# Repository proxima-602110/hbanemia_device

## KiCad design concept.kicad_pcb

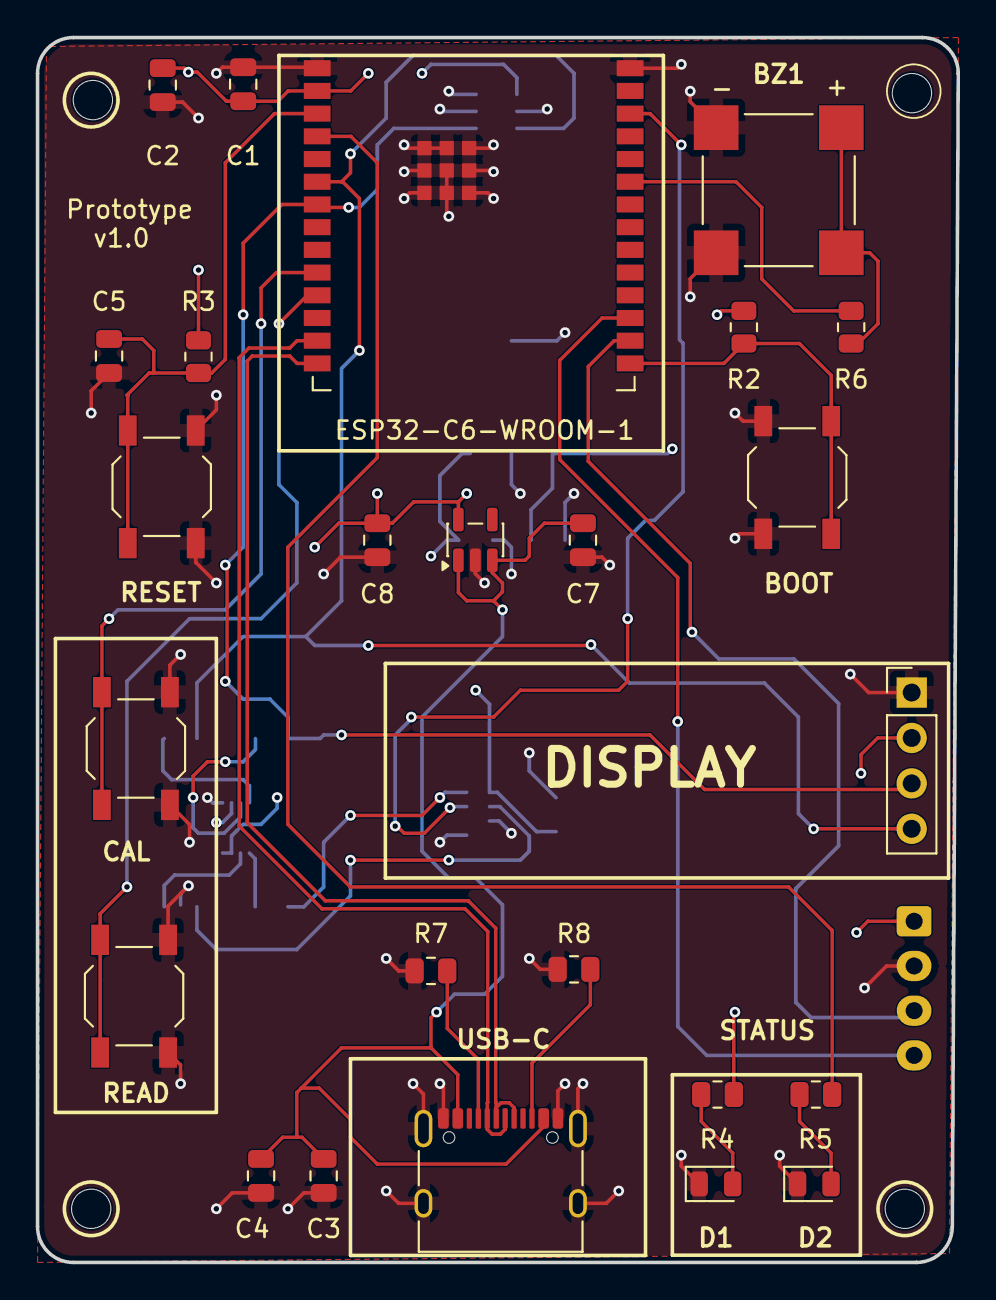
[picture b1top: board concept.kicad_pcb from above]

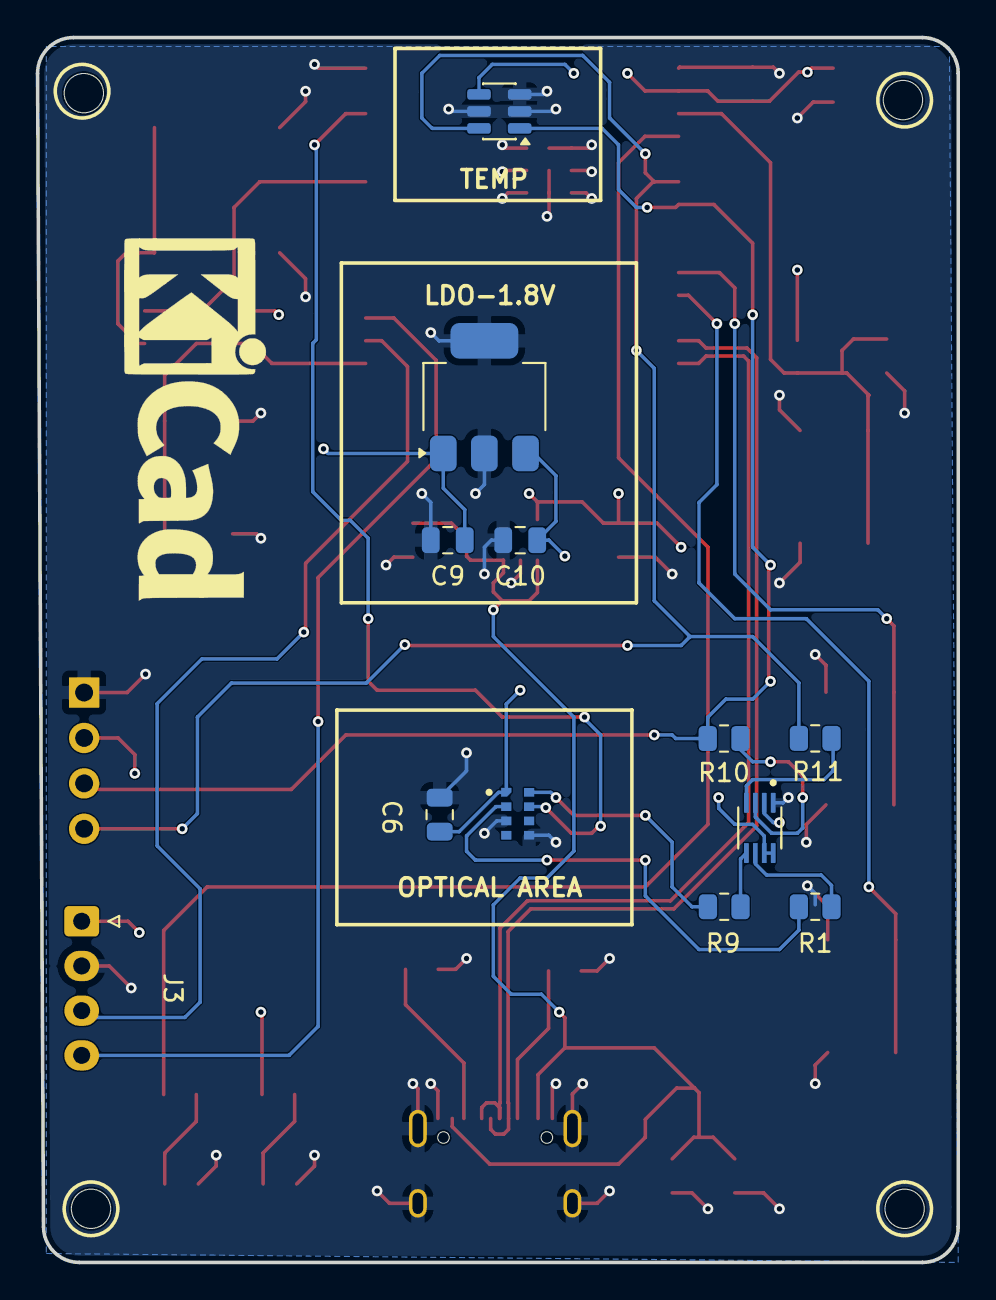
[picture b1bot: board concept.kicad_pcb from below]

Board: 4 copper layers, 51.5 x 68.5 mm, 41 parts (12 on the bottom side), 28 nets.

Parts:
BZ1: Buzzer; XDCR_CMT-8504-100-SMT-TR
C1, C4, C5, C6: 0.1u; C_0805_2012Metric
C2, C3, C9, C10: 10u; C_0805_2012Metric
C7, C8: 1u; C_0805_2012Metric
D1: PWR; LED_0805_2012Metric
D2: Wi-Fi; LED_0805_2012Metric
H1, H2, H3, H4: MountingHole; MountingHole_2.2mm_M2
J1: USB_C_Receptacle_USB2.0_16P; USB_C_Receptacle_XKB_U262-16XN-4BVC11
J2: Conn_01x04; PinHeader_1x04_P2.54mm_Vertical
J3: Conn_01x04; JST_XH_S4B-XH-A-1_1x04_P2.50mm_Horizontal
R1, R9, R10, R11: 4.7k; R_0805_2012Metric
R2, R3: 10k; R_0805_2012Metric
R4, R5, R6: 220; R_0805_2012Metric
R7, R8: 5.1k; R_0805_2012Metric
SW1, SW2, SW3, SW4: SW_Push; SW_SPST_TL3342
U1: AP2112K-3.3; SOT-23-5
U2: AS7341DLG; XDCR_AS7341-DLGM
U3: TMP100; SOT-23-6
U4: LT1963AxST-1.8; SOT-223-3_TabPin2
U5: PCA9306; SOP50P310X90-8N
U6: ESP32-C6-WROOM-1

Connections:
+1.8V: C6.1, C10.1, U2.1 (VDD), U4.3 (OUT), U5.2 (VREF1)
+3.3V: C1.1, C2.1, C8.1, C9.1, J2.2, J3.1, R2.1, R3.1, R4.2, U1.5 (VOUT), U3.4 (V+), U4.1 (IN), U5.7 (VREF2), U5.8 (EN), U6.2 (3V3)
/BOOT: R2.2, SW2.1, U6.15 (GPIO9)
/EN: C5.1, R3.2, SW1.1, U6.3 (EN/CHIP_PU)
/IO3: U2.7 (INT), U6.26 (GPIO3/ADC1_CH3)
/IO4: R5.2, U6.4 (MTMS/GPIO4/ADC1_CH4)
/IO6: J2.4, R11.1, U3.6 (SDA), U6.6 (MTCK/GPIO6/ADC1_CH6)
/IO7: J2.3, R10.1, U3.1 (SCL), U6.7 (MTDO/GPIO7)
/IO10: SW4.1, U6.10 (GPIO8)
/IO11: SW3.1, U6.11 (GPIO10)
/IO15: R6.2, U6.23 (GPIO15)
/LED_560: J3.3, U6.16 (GPIO18)
/LED_850: J3.4, U6.17 (GPIO19)
/USB_D+: J1.A6 (D+), J1.B6 (D+), U6.14 (GPIO13/USB_D+)
/USB_D-: J1.A7 (D-), J1.B7 (D-), U6.13 (GPIO12/USB_D-)
GND: BZ1.2 (-), C1.2, C2.2, C3.2, C4.2, C5.2, C6.2, C7.2, C8.2, C9.2, C10.2, D1.1 (K), D2.1 (K), J1.A1 (GND), J1.A12 (GND), J1.B1 (GND), J1.B12 (GND), J1.SH (SHIELD), J2.1, J3.2, R7.1, R8.1, SW1.2, SW2.2, SW3.2, SW4.2, U1.2 (GND), U2.3 (GND), U2.5 (PGND), U3.2 (GND), U3.3 (ADD1), U3.5 (ADD0), U4.2 (GND), U5.1 (GND), U6.1 (GND), U6.28 (GND), U6.29 (GND)
unnamed: BZ1.1 (+), R6.1
unnamed: D1.2 (A), R4.1
unnamed: D2.2 (A), R5.1
unnamed: J1.A5 (CC1), R7.2
unnamed: J1.B5 (CC2), R8.2
unnamed: C3.1, C4.1, C7.1, J1.A4 (VBUS), J1.A9 (VBUS), J1.B4 (VBUS), J1.B9 (VBUS), U1.1 (VIN), U1.3 (EN)
unnamed: R1.2, U2.2 (SCL)
unnamed: R9.2, U2.8 (SDA)
unnamed: R10.2, U5.3 (SCL1)
unnamed: R1.1, U5.6 (SCL2)
unnamed: R11.2, U5.4 (SDA1)
unnamed: R9.1, U5.5 (SDA2)

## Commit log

2026-05-16 Added updated schematic to repo
2026-05-25 Added .pcb file
